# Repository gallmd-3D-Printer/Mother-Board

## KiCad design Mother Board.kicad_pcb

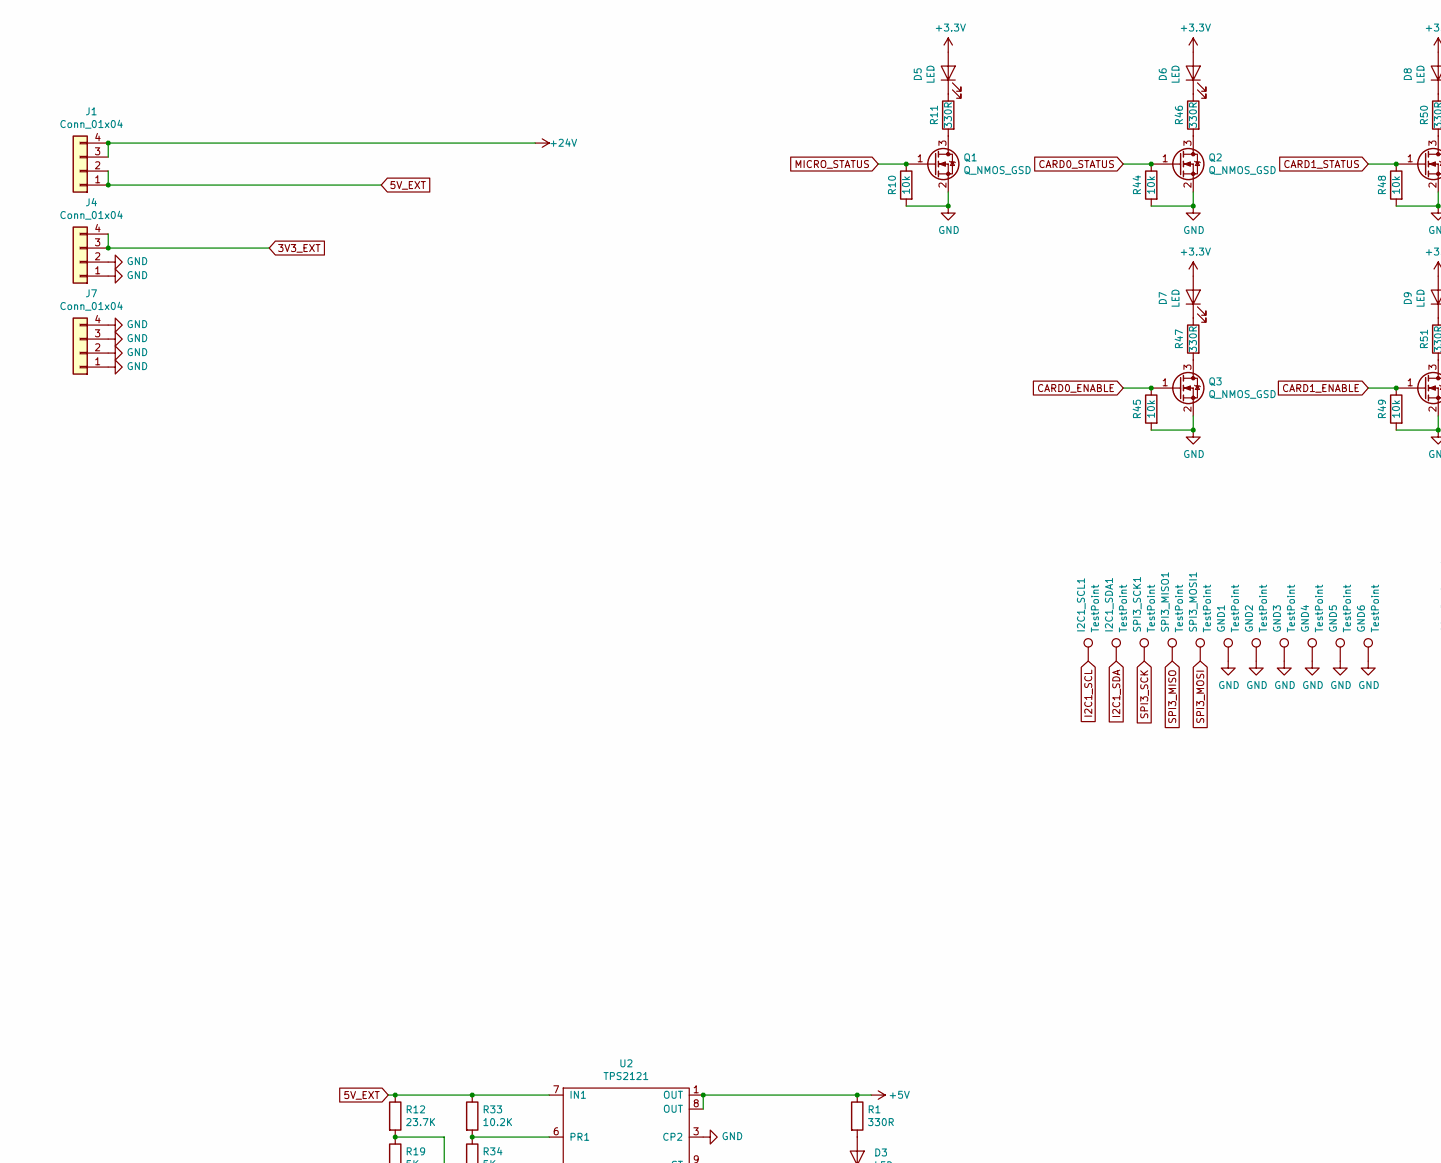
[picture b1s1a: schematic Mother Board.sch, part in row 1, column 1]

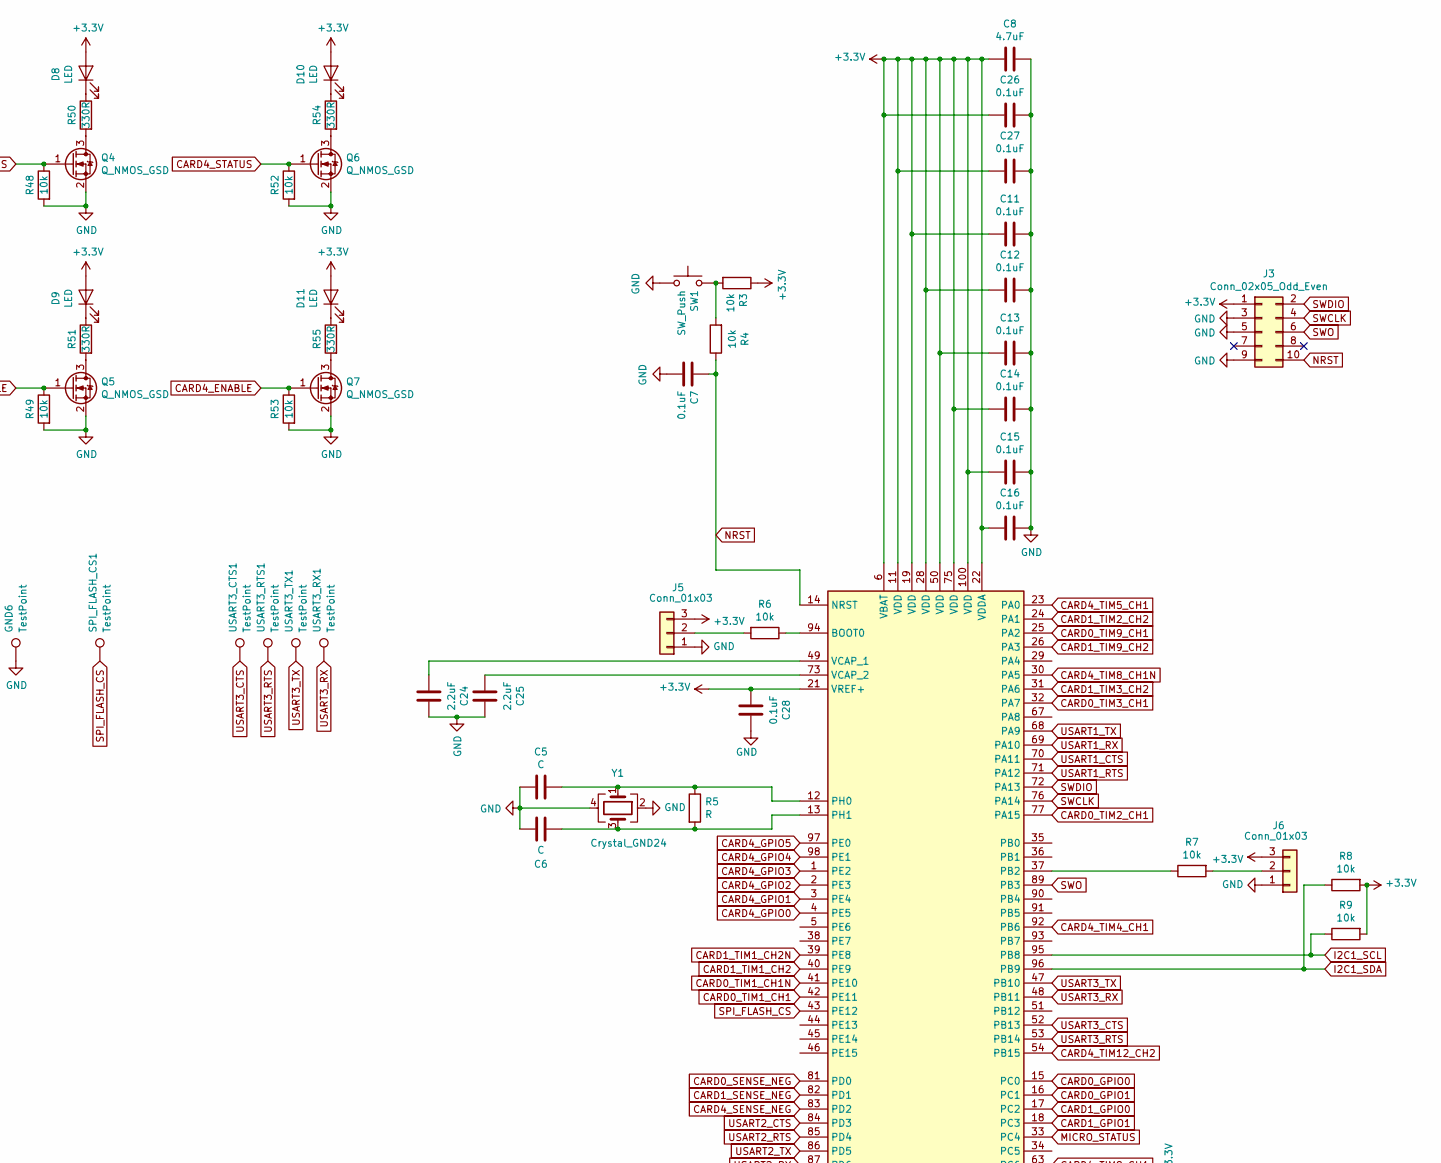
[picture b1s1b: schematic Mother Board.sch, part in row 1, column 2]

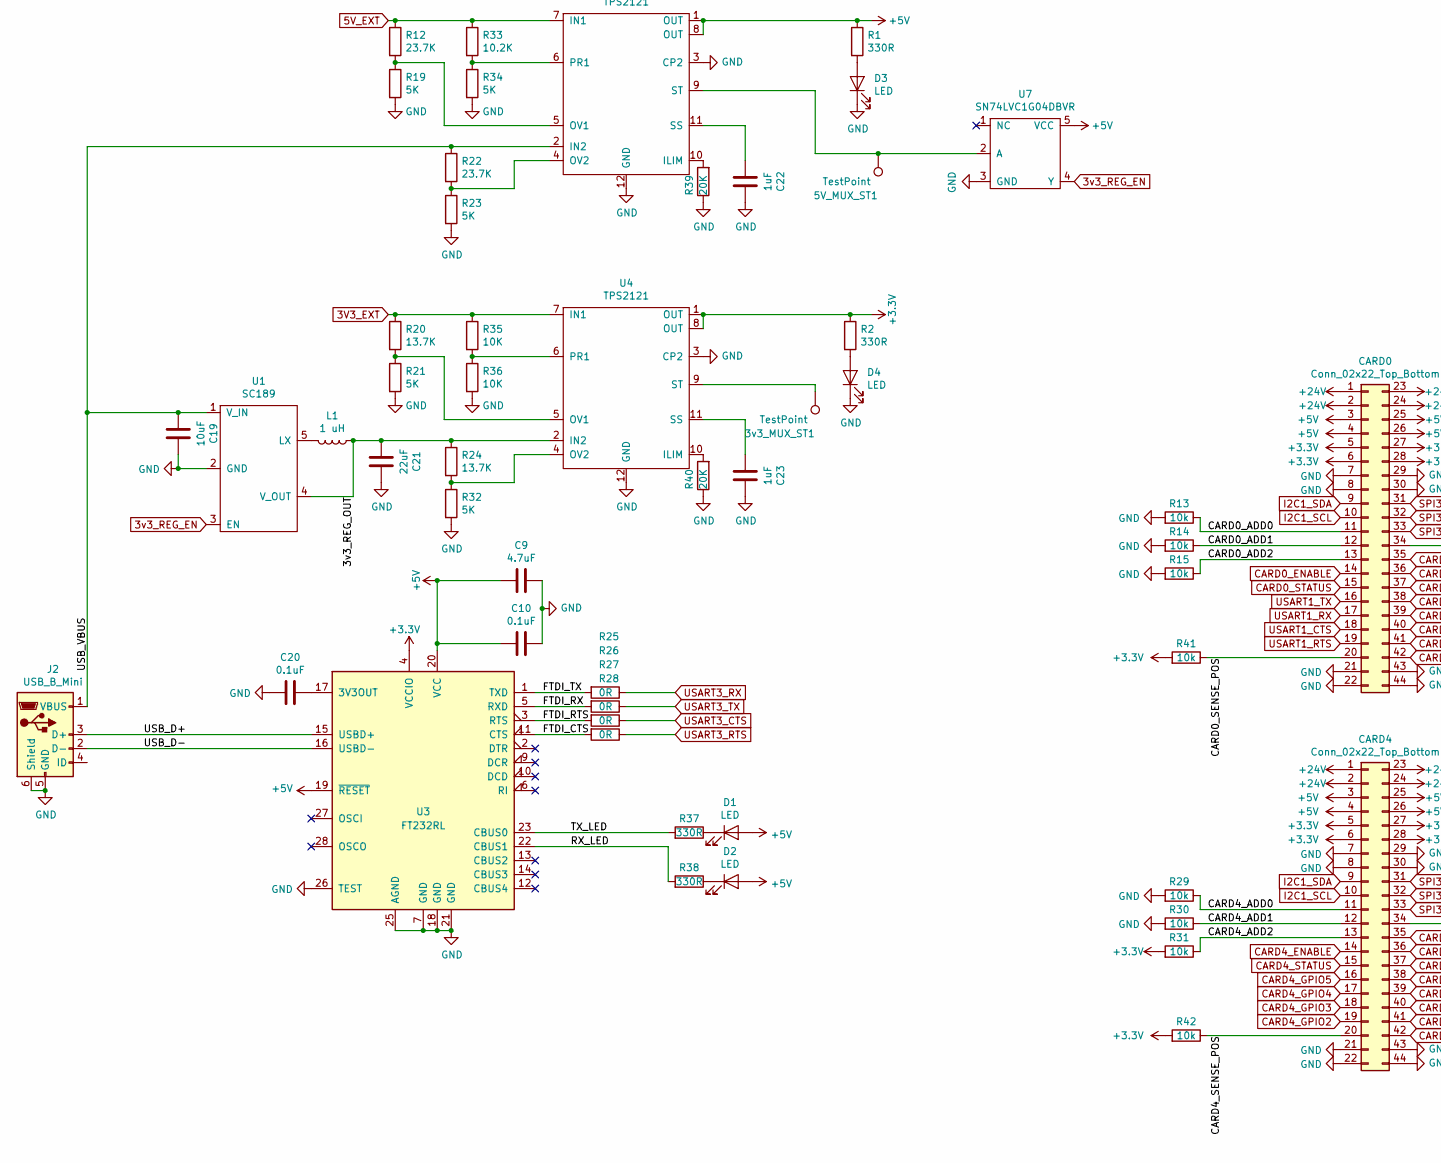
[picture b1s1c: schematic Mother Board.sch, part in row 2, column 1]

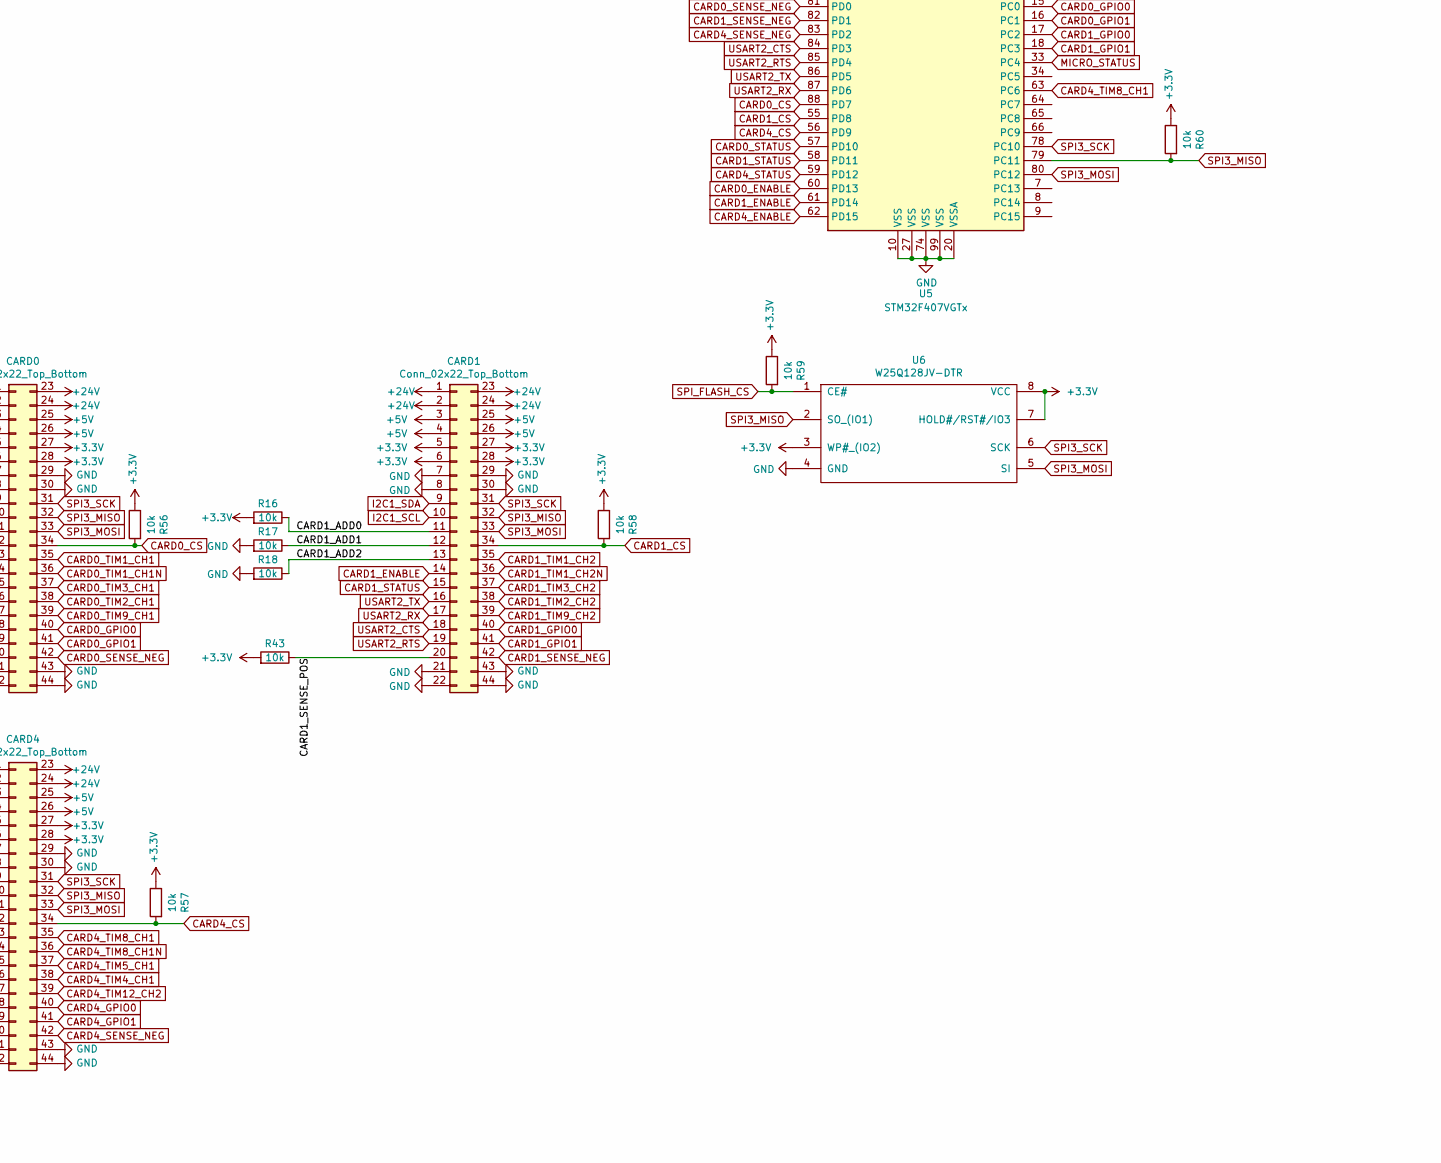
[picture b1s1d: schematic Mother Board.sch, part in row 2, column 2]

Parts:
3v3_MUX_ST1, 5V_MUX_ST1: TestPoint; TestPoint_Pad_D1.0mm
C5, C6: C; C_0603_1608Metric_Pad1.05x0.95mm_HandSolder
C7, C10, C11, C12, C13, C14, C15, C16, C20, C26, C27, C28: 0.1uF; C_0603_1608Metric_Pad1.05x0.95mm_HandSolder
C8, C9: 4.7uF; C_0603_1608Metric_Pad1.05x0.95mm_HandSolder
C19: 10uF; C_0603_1608Metric_Pad1.05x0.95mm_HandSolder
C21: 22uF; C_0603_1608Metric_Pad1.05x0.95mm_HandSolder
C22, C23: 1uF; C_0603_1608Metric_Pad1.05x0.95mm_HandSolder
C24, C25: 2.2uF; C_0603_1608Metric_Pad1.05x0.95mm_HandSolder
CARD0, CARD1, CARD4: Conn_02x22_Top_Bottom; 5530843-4; Part Number 5530843-4
D1, D2: LED; LED_1206_3216Metric_Pad1.42x1.75mm_HandSolder
D3, D4, D5, D6, D7, D8, D9, D10, D11: LED; LED_1206_3216Metric_Pad1.42x1.75mm_HandSolder; Part Number RED LED 1206
GND1, GND2, GND3, GND4, GND5, GND6: TestPoint; TestPoint_Keystone_5015_Micro-Minature; Part Number 5015
I2C1_SCL1, I2C1_SDA1: TestPoint; TestPoint_Keystone_5015_Micro-Minature; Part Number 5015
J1, J4, J7: Conn_01x04; TerminalBlock_bornier-4_P5.08mm; Part Number 796638-4
J2: USB_B_Mini; USB_Mini-B_Lumberg_2486_01_Horizontal
J3: Conn_02x05_Odd_Even; PinHeader_2x05_P1.27mm_Vertical; Part Number FTSH-105-01-F-D-K
J5, J6: Conn_01x03; PinHeader_1x03_P2.54mm_Vertical
L1: 1 uH; L_1206_3216Metric; Part Number CIGW252010GL1R0MNE
Q1, Q2, Q3, Q4, Q5, Q6, Q7: Q_NMOS_GSD; SOT-323_SC-70_Handsoldering; Part Number 2N7002BKVL
R1, R2, R11, R37, R38, R46, R47, R50, R51, R54, R55: 330R; R_0603_1608Metric_Pad1.05x0.95mm_HandSolder
R3, R4, R6, R7, R8, R9, R10, R13, R14, R15, R16, R17, R18, R29, R30, R31, R41, R42, R43, R44, R45, R48, R49, R52, R53, R56, R57, R58, R59, R60: 10k; R_0603_1608Metric_Pad1.05x0.95mm_HandSolder
R5: R; R_0603_1608Metric_Pad1.05x0.95mm_HandSolder
R12, R22: 23.7K; R_0603_1608Metric_Pad1.05x0.95mm_HandSolder
R19, R21, R23, R32, R34: 5K; R_0603_1608Metric_Pad1.05x0.95mm_HandSolder
R20, R24: 13.7K; R_0603_1608Metric_Pad1.05x0.95mm_HandSolder
R25, R26, R27, R28: 0R; R_0603_1608Metric_Pad1.05x0.95mm_HandSolder
R33: 10.2K; R_0603_1608Metric_Pad1.05x0.95mm_HandSolder
R35, R36: 10K; R_0603_1608Metric_Pad1.05x0.95mm_HandSolder
R39, R40: 20K; R_0603_1608Metric_Pad1.05x0.95mm_HandSolder
SPI3_MISO1, SPI3_MOSI1, SPI3_SCK1: TestPoint; TestPoint_Keystone_5015_Micro-Minature; Part Number 5015
SPI_FLASH_CS1: TestPoint; TestPoint_Keystone_5015_Micro-Minature; Part Number 5015
SW1: SW_Push; FSM2JMTR; Part Number FSM2JMTR
U1: SC189; SOT-23-5_HandSoldering; Part Number SC189
U2, U4: TPS2121; Texas_VQFN_HR_12; Part Number TPS2121
U3: FT232RL; SSOP-28_5.3x10.2mm_P0.65mm; Part Number FT232RL
U5: STM32F407VGTx; LQFP-100_14x14mm_P0.5mm; Part Number STM32F407VGT6
U6: W25Q128JV-DTR; SOIC-8_3.9x4.9mm_P1.27mm; Part Number W25Q128JVSIQ
U7: SN74LVC1G04DBVR; SOT-23-5_HandSoldering; Part Number SN74LVC1G04DBVR
USART3_CTS1, USART3_RTS1, USART3_RX1, USART3_TX1: TestPoint; TestPoint_Keystone_5015_Micro-Minature; Part Number 5015
Y1: Crystal_GND24; Crystal_SMD_SeikoEpson_TSX3225-4Pin_3.2x2.5mm_HandSoldering; Part Number TSX-3225 26.0000MF09Z-AC3

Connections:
3V3_EXT: J4.3, J4.4, R20.1, R35.1, U4.7 (IN1)
3v3_REG_EN: U1.3 (EN), U7.4 (Y)
5V_EXT: J1.1, J1.2, R12.1, R33.1, U2.7 (IN1)
+3V3: C8.2, C11.2, C12.2, C13.2, C14.2, C15.2, C16.2, C26.2, C27.2, C28.2, CARD0.5, CARD0.6, CARD0.27, CARD0.28, CARD1.5, CARD1.6, CARD1.27, CARD1.28, CARD4.5, CARD4.6, CARD4.27, CARD4.28, D5.2 (A), D6.2 (A), D7.2 (A), D8.2 (A), D9.2 (A), D10.2 (A), D11.2 (A), J3.1, J5.3, J6.3, R2.1, R3.1, R8.2, R9.2, R16.2, R31.2, R41.2, R42.2, R43.2, R56.1, R57.1, R58.1, R59.1, R60.1, U3.4 (VCCIO), U4.1 (OUT), U4.8 (OUT), U5.6 (VBAT), U5.11 (VDD), U5.19 (VDD), U5.21 (VREF+), U5.22 (VDDA), U5.28 (VDD), U5.50 (VDD), U5.75 (VDD), U5.100 (VDD), U6.3 (WP#_(IO2)), U6.7 (HOLD#/RST#/IO3), U6.8 (VCC)
+5V: C9.2, C10.2, CARD0.3, CARD0.4, CARD0.25, CARD0.26, CARD1.3, CARD1.4, CARD1.25, CARD1.26, CARD4.3, CARD4.4, CARD4.25, CARD4.26, D1.2 (A), D2.2 (A), R1.1, U2.1 (OUT), U2.8 (OUT), U3.19 (~RESET~), U3.20 (VCC), U7.5 (VCC)
+24V: CARD0.1, CARD0.2, CARD0.23, CARD0.24, CARD1.1, CARD1.2, CARD1.23, CARD1.24, CARD4.1, CARD4.2, CARD4.23, CARD4.24, J1.3, J1.4
/3v3_REG_OUT: C21.2, L1.1, R24.1, U1.4 (V_OUT), U4.2 (IN2)
/CARD0_ADD0: CARD0.11, R13.1
/CARD0_ADD1: CARD0.12, R14.1
/CARD0_ADD2: CARD0.13, R15.1
/CARD0_SENSE_POS: CARD0.20, R41.1
/CARD1_ADD0: CARD1.11, R16.1
/CARD1_ADD1: CARD1.12, R17.1
/CARD1_ADD2: CARD1.13, R18.1
/CARD1_SENSE_POS: CARD1.20, R43.1
/CARD4_ADD0: CARD4.11, R29.1
/CARD4_ADD1: CARD4.12, R30.1
/CARD4_ADD2: CARD4.13, R31.1
/CARD4_SENSE_POS: CARD4.20, R42.1
/FTDI_CTS: R28.2, U3.11 (CTS)
/FTDI_RTS: R27.2, U3.3 (RTS)
/FTDI_RX: R26.2, U3.5 (RXD)
/FTDI_TX: R25.2, U3.1 (TXD)
/RX_LED: R38.2, U3.22 (CBUS1)
/TX_LED: R37.2, U3.23 (CBUS0)
/USB_D+: J2.3 (D+), U3.15 (USBD+)
/USB_D-: J2.2 (D-), U3.16 (USBD-)
/USB_VBUS: C19.2, J2.1 (VBUS), R22.1, U1.1 (V_IN), U2.2 (IN2)
CARD0_CS: CARD0.34, R56.2, U5.88 (PD7)
CARD0_ENABLE: CARD0.14, Q3.1 (G), R45.1, U5.60 (PD13)
CARD0_GPIO0: CARD0.40, U5.15 (PC0)
CARD0_GPIO1: CARD0.41, U5.16 (PC1)
CARD0_SENSE_NEG: CARD0.42, U5.81 (PD0)
CARD0_STATUS: CARD0.15, Q2.1 (G), R44.1, U5.57 (PD10)
CARD0_TIM1_CH1: CARD0.35, U5.42 (PE11)
CARD0_TIM1_CH1N: CARD0.36, U5.41 (PE10)
CARD0_TIM2_CH1: CARD0.38, U5.77 (PA15)
CARD0_TIM3_CH1: CARD0.37, U5.32 (PA7)
CARD0_TIM9_CH1: CARD0.39, U5.25 (PA2)
CARD1_CS: CARD1.34, R58.2, U5.55 (PD8)
CARD1_ENABLE: CARD1.14, Q5.1 (G), R49.1, U5.61 (PD14)
CARD1_GPIO0: CARD1.40, U5.17 (PC2)
CARD1_GPIO1: CARD1.41, U5.18 (PC3)
CARD1_SENSE_NEG: CARD1.42, U5.82 (PD1)
CARD1_STATUS: CARD1.15, Q4.1 (G), R48.1, U5.58 (PD11)
CARD1_TIM1_CH2: CARD1.35, U5.40 (PE9)
CARD1_TIM1_CH2N: CARD1.36, U5.39 (PE8)
CARD1_TIM2_CH2: CARD1.38, U5.24 (PA1)
CARD1_TIM3_CH2: CARD1.37, U5.31 (PA6)
CARD1_TIM9_CH2: CARD1.39, U5.26 (PA3)
CARD4_CS: CARD4.34, R57.2, U5.56 (PD9)
CARD4_ENABLE: CARD4.14, Q7.1 (G), R53.1, U5.62 (PD15)
CARD4_GPIO0: CARD4.40, U5.4 (PE5)
CARD4_GPIO1: CARD4.41, U5.3 (PE4)
CARD4_GPIO2: CARD4.19, U5.2 (PE3)
CARD4_GPIO3: CARD4.18, U5.1 (PE2)
CARD4_GPIO4: CARD4.17, U5.98 (PE1)
CARD4_GPIO5: CARD4.16, U5.97 (PE0)
CARD4_SENSE_NEG: CARD4.42, U5.83 (PD2)
CARD4_STATUS: CARD4.15, Q6.1 (G), R52.1, U5.59 (PD12)
CARD4_TIM4_CH1: CARD4.38, U5.92 (PB6)
CARD4_TIM5_CH1: CARD4.37, U5.23 (PA0)
CARD4_TIM8_CH1: CARD4.35, U5.63 (PC6)
CARD4_TIM8_CH1N: CARD4.36, U5.30 (PA5)
CARD4_TIM12_CH2: CARD4.39, U5.54 (PB15)
GND: C5.2, C6.2, C7.2, C8.1, C9.1, C10.1, C11.1, C12.1, C13.1, C14.1, C15.1, C16.1, C19.1, C20.2, C21.1, C22.1, C23.1, C24.1, C25.1, C26.1, C27.1, C28.1, CARD0.7, CARD0.8, CARD0.21, CARD0.22, CARD0.29, CARD0.30, CARD0.43, CARD0.44, CARD1.7, CARD1.8, CARD1.21, CARD1.22, CARD1.29, CARD1.30, CARD1.43, CARD1.44, CARD4.7, CARD4.8, CARD4.21, CARD4.22, CARD4.29, CARD4.30, CARD4.43, CARD4.44, D3.1 (K), D4.1 (K), GND1.1, GND2.1, GND3.1, GND4.1, GND5.1, GND6.1, J2.5 (GND), J2.6 (Shield), J3.3, J3.5, J3.9, J4.1, J4.2, J5.1, J6.1, J7.1, J7.2, J7.3, J7.4, Q1.2 (S), Q2.2 (S), Q3.2 (S), Q4.2 (S), Q5.2 (S), Q6.2 (S), Q7.2 (S), R10.2, R13.2, R14.2, R15.2, R17.2, R18.2, R19.2, R21.2, R23.2, R29.2, R30.2, R32.2, R34.2, R36.2, R39.1, R40.1, R44.2, R45.2, R48.2, R49.2, R52.2, R53.2, SW1.1, U1.2 (GND), U2.3 (CP2), U2.12 (GND), U3.7 (GND), U3.18 (GND), U3.21 (GND), U3.25 (AGND), U3.26 (TEST), U4.3 (CP2), U4.12 (GND), U5.10 (VSS), U5.20 (VSSA), U5.27 (VSS), U5.74 (VSS), U5.99 (VSS), U6.4 (GND), U7.3 (GND), Y1.2, Y1.4
I2C1_SCL: CARD0.10, CARD1.10, CARD4.10, I2C1_SCL1.1, R9.1, U5.95 (PB8)
I2C1_SDA: CARD0.9, CARD1.9, CARD4.9, I2C1_SDA1.1, R8.1, U5.96 (PB9)
MICRO_STATUS: Q1.1 (G), R10.1, U5.33 (PC4)
NRST: C7.1, J3.10, R4.1, U5.14 (NRST)
unnamed: 3v3_MUX_ST1.1, U4.9 (ST)
unnamed: 5V_MUX_ST1.1, U2.9 (ST), U7.2 (A)
unnamed: C5.1, R5.1, U5.12 (PH0), Y1.1
unnamed: C6.1, R5.2, U5.13 (PH1), Y1.3
unnamed: C20.1, U3.17 (3V3OUT)
unnamed: C22.2, U2.11 (SS)
unnamed: C23.2, U4.11 (SS)
unnamed: C24.2, U5.49 (VCAP_1)
unnamed: C25.2, U5.73 (VCAP_2)
unnamed: D1.1 (K), R37.1
unnamed: D2.1 (K), R38.1
unnamed: D3.2 (A), R1.2
unnamed: D4.2 (A), R2.2
unnamed: D5.1 (K), R11.1
unnamed: D6.1 (K), R46.1
unnamed: D7.1 (K), R47.1
unnamed: D8.1 (K), R50.1
unnamed: D9.1 (K), R51.1
unnamed: D10.1 (K), R54.1
unnamed: D11.1 (K), R55.1
unnamed: J5.2, R6.2
unnamed: J6.2, R7.2
unnamed: L1.2, U1.5 (LX)
unnamed: Q1.3 (D), R11.2
unnamed: Q2.3 (D), R46.2
unnamed: Q3.3 (D), R47.2
unnamed: Q4.3 (D), R50.2
unnamed: Q5.3 (D), R51.2
unnamed: Q6.3 (D), R54.2
unnamed: Q7.3 (D), R55.2
unnamed: R3.2, R4.2, SW1.2
unnamed: R6.1, U5.94 (BOOT0)
unnamed: R7.1, U5.37 (PB2)
unnamed: R12.2, R19.1, U2.5 (OV1)
unnamed: R20.2, R21.1, U4.5 (OV1)
unnamed: R22.2, R23.1, U2.4 (OV2)
unnamed: R24.2, R32.1, U4.4 (OV2)
unnamed: R33.2, R34.1, U2.6 (PR1)
unnamed: R35.2, R36.1, U4.6 (PR1)
unnamed: R39.2, U2.10 (ILIM)
unnamed: R40.2, U4.10 (ILIM)
SPI3_MISO: CARD0.32, CARD1.32, CARD4.32, R60.2, SPI3_MISO1.1, U5.79 (PC11), U6.2 (SO_(IO1))
SPI3_MOSI: CARD0.33, CARD1.33, CARD4.33, SPI3_MOSI1.1, U5.80 (PC12), U6.5 (SI)
SPI3_SCK: CARD0.31, CARD1.31, CARD4.31, SPI3_SCK1.1, U5.78 (PC10), U6.6 (SCK)
SPI_FLASH_CS: R59.2, SPI_FLASH_CS1.1, U5.43 (PE12), U6.1 (CE#)
SWCLK: J3.4, U5.76 (PA14)
SWDIO: J3.2, U5.72 (PA13)
SWO: J3.6, U5.89 (PB3)
USART1_CTS: CARD0.18, U5.70 (PA11)
USART1_RTS: CARD0.19, U5.71 (PA12)
USART1_RX: CARD0.17, U5.69 (PA10)
USART1_TX: CARD0.16, U5.68 (PA9)
USART2_CTS: CARD1.18, U5.84 (PD3)
USART2_RTS: CARD1.19, U5.85 (PD4)
USART2_RX: CARD1.17, U5.87 (PD6)
USART2_TX: CARD1.16, U5.86 (PD5)
USART3_CTS: R27.1, U5.52 (PB13), USART3_CTS1.1
USART3_RTS: R28.1, U5.53 (PB14), USART3_RTS1.1
USART3_RX: R25.1, U5.48 (PB11), USART3_RX1.1
USART3_TX: R26.1, U5.47 (PB10), USART3_TX1.1

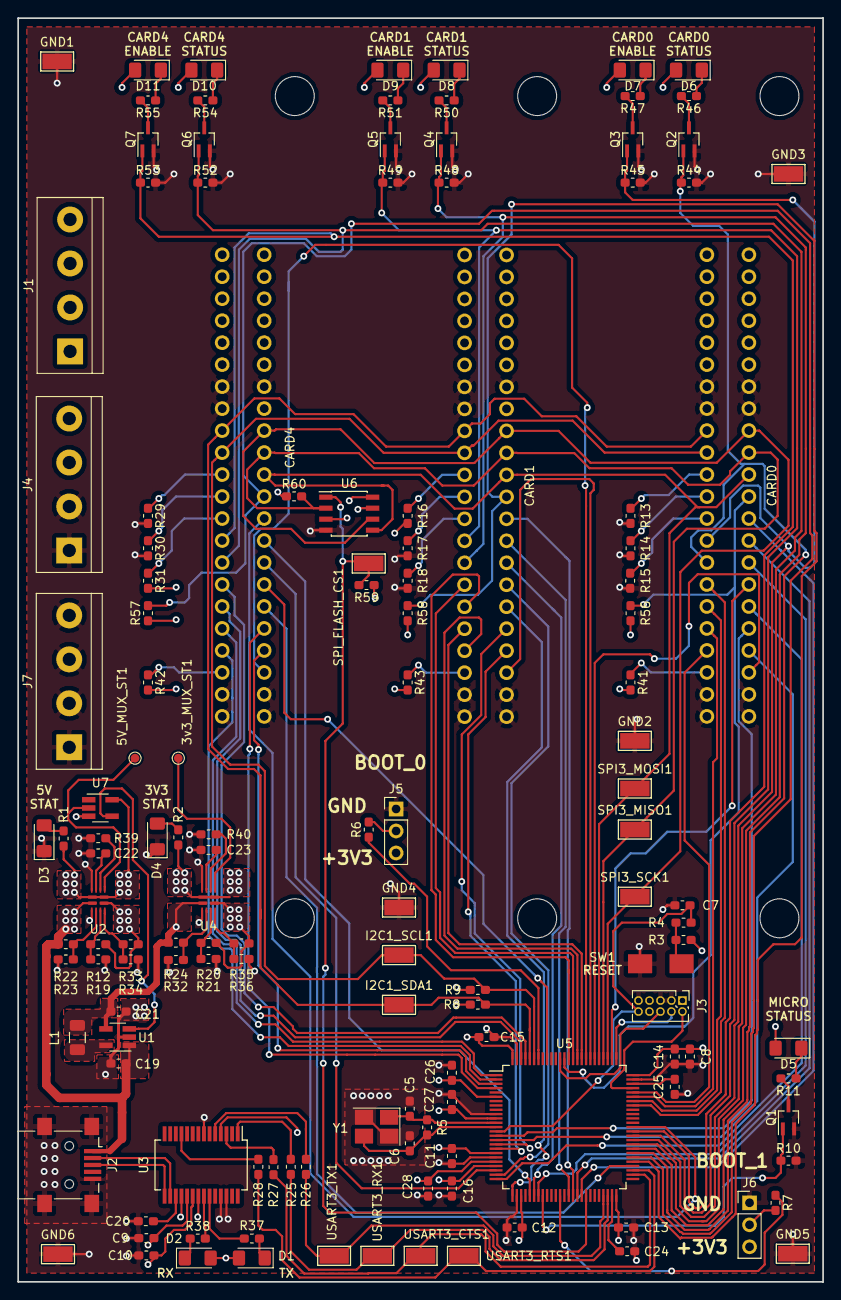
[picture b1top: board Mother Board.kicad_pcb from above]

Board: 4 copper layers, 93.0 x 146.0 mm, 138 parts (0 on the bottom side), 130 nets.

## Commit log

2019-07-23 Finished labeling card pins, changed rough layout
2019-07-25 Moved power supply to external board. Reworked rough layout
2019-08-10 last commit before shifting to prototype version
2019-08-28 worked on layout for power mux section
2019-08-30 worked on layout of power mux, added inverter to enable 3v3 regulator
2019-09-16 all tracks connected, need to clean up layout before ordering.
2019-10-02 Needs final clean up, then ready for ordering
2019-10-08 added part numbers to schematic, pcb ordered
